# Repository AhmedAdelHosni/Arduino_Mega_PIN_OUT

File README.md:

# Arduino_Mega_PIN_OUT
Board layout pcb for expanding the Arduino Mega pin to Terminal block 5 mm pitch.

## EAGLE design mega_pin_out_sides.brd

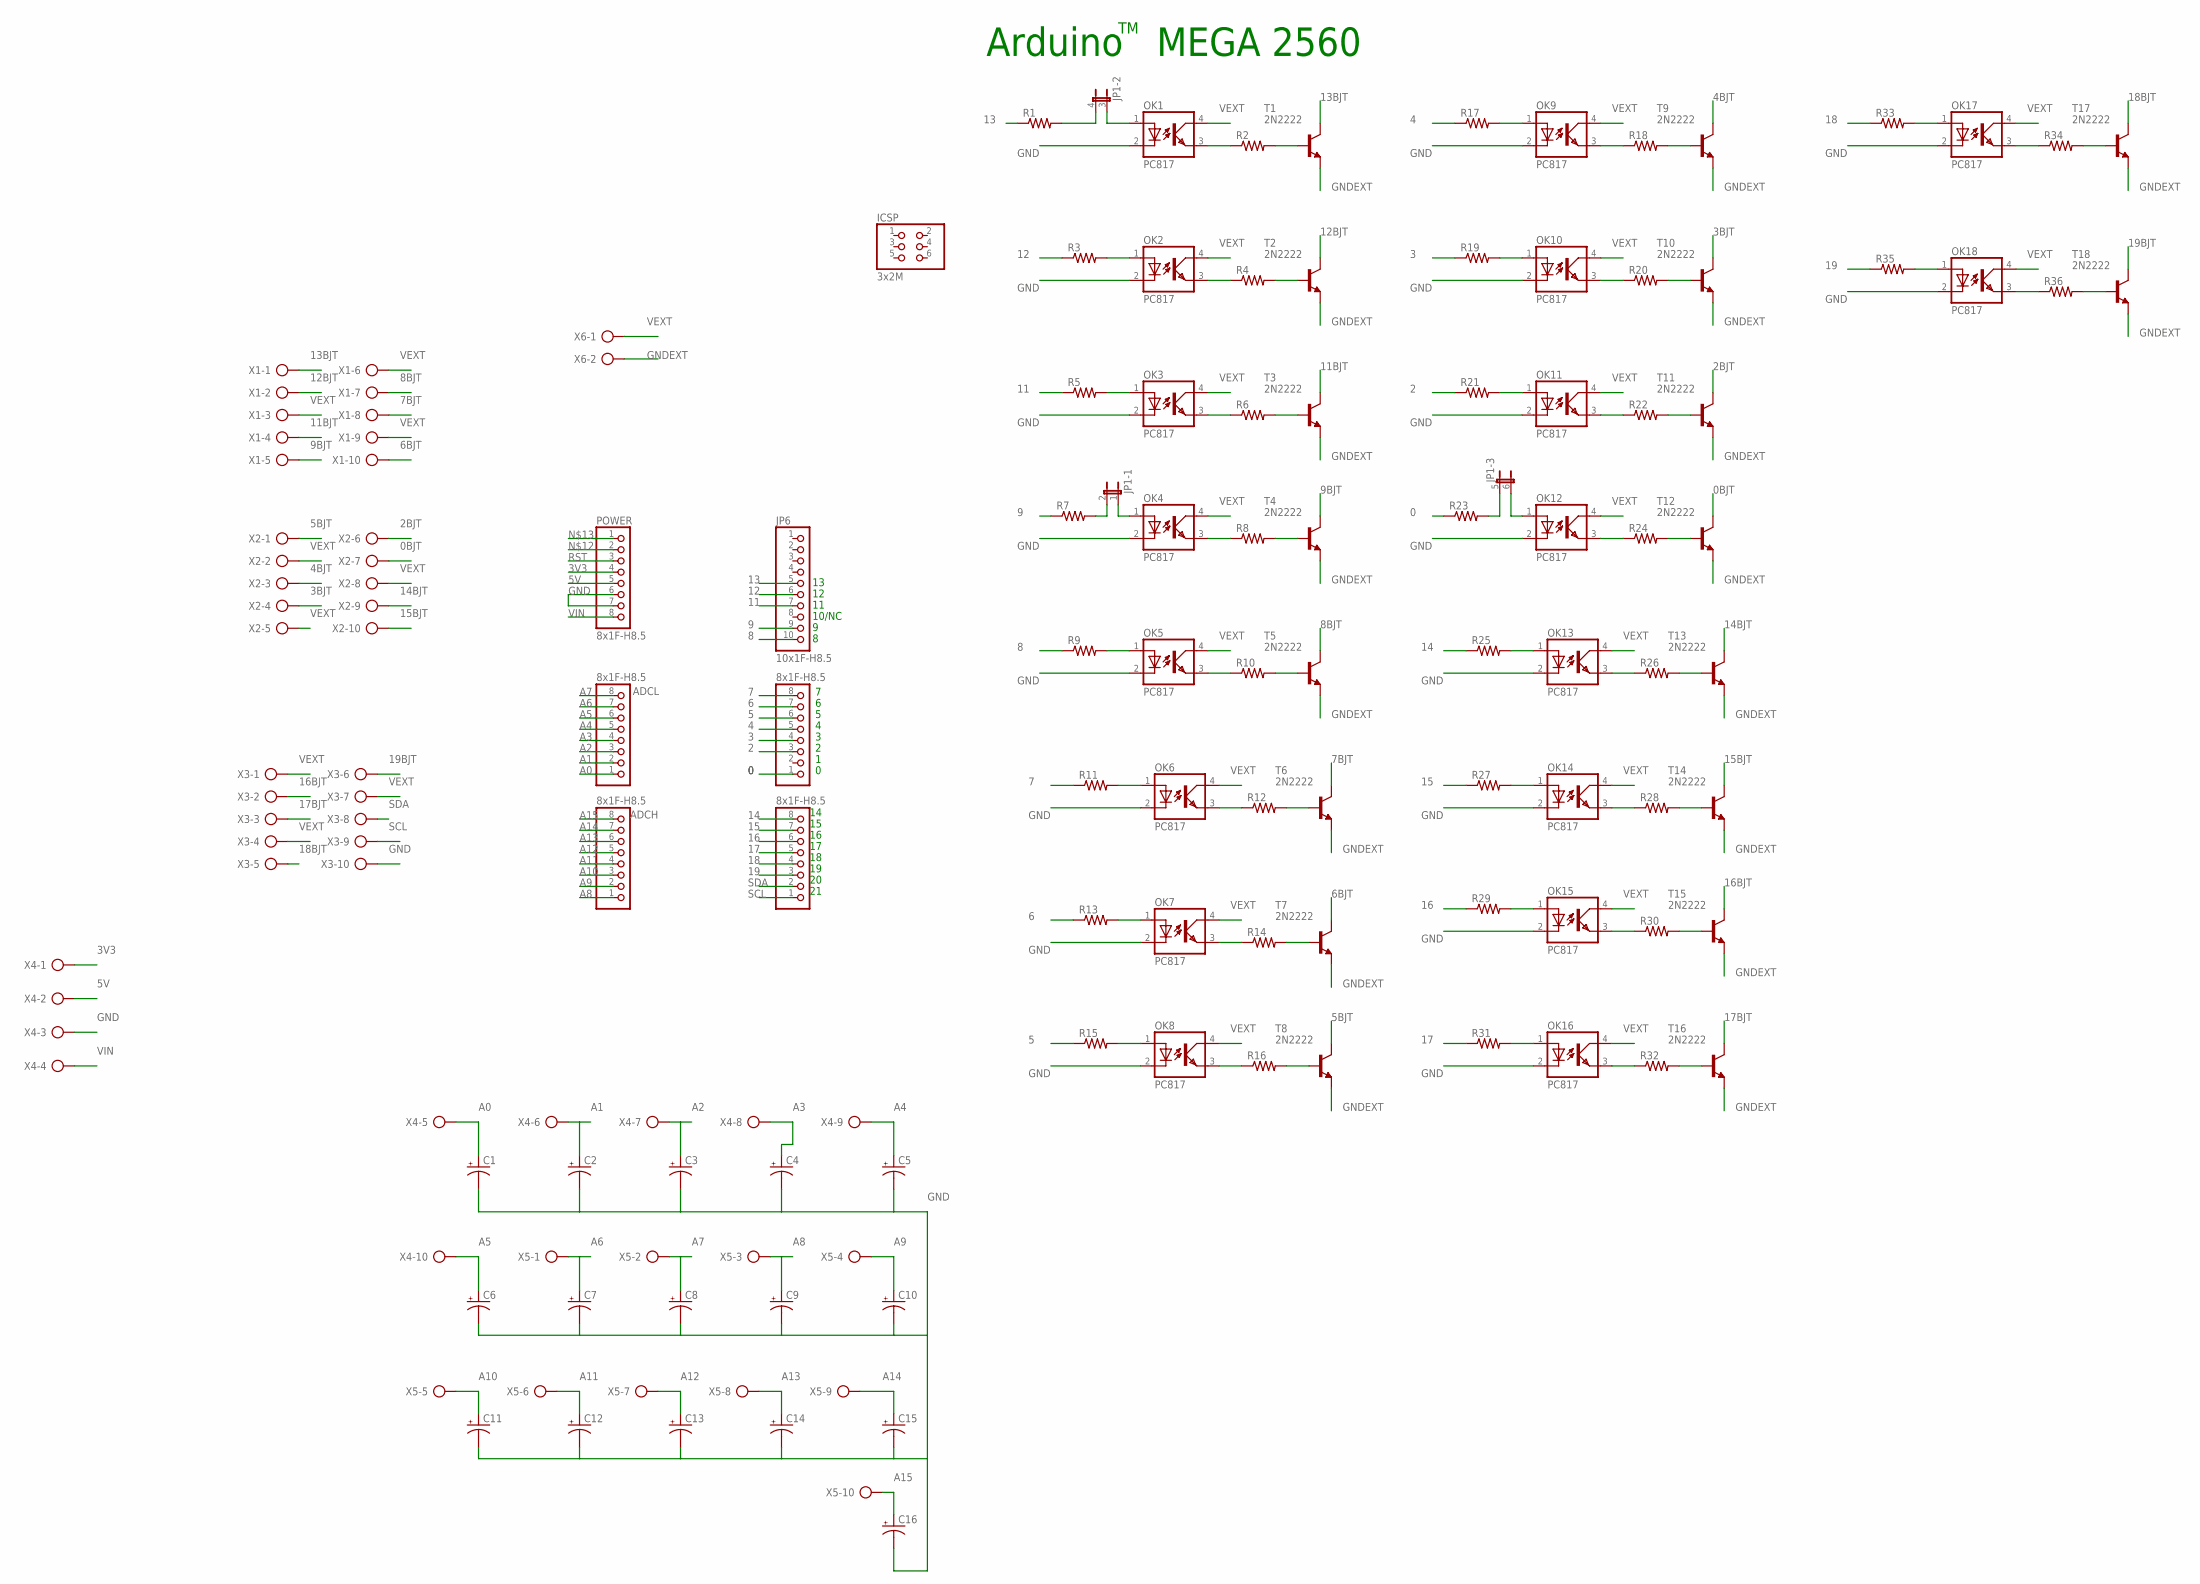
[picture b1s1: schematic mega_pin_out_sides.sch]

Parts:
ADCH: 8x1F-H8.5; 1X08
ADCL: 8x1F-H8.5; 1X08
C1, C2, C3, C4, C5, C6, C7, C8, C9, C10, C11, C12, C13, C14, C15, C16: CPOL-USE2-4; E2-4
COMMUNICATION: 8x1F-H8.5; 1X08
ICSP: 3x2M; 2X03
JP1: JP3QE; JP3Q
JP6: 10x1F-H8.5; 1X10
OK1, OK2, OK3, OK4, OK5, OK6, OK7, OK8, OK9, OK10, OK11, OK12, OK13, OK14, OK15, OK16, OK17, OK18: PC817; DIL04
POWER: 8x1F-H8.5; 1X08
PWML: 8x1F-H8.5; 1X08
R1, R2, R3, R4, R5, R6, R7, R8, R9, R10, R11, R12, R13, R14, R15, R16, R17, R18, R19, R20, R21, R22, R23, R24, R25, R26, R27, R28, R29, R30, R31, R32, R33, R34, R35, R36: R-US_M1206; M1206
T1, T2, T3, T4, T5, T6, T7, T8, T9, T10, T11, T12, T13, T14, T15, T16, T17, T18: 2N2222; TO18
X1, X2, X3, X4, X5: AK500/10
X6: AK500/2

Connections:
0: PWML.1, R23.1
0BJT: T12.3 (C), X2.7
2: PWML.3, R21.1
2BJT: T11.3 (C), X2.6
3: PWML.4, R19.1
3BJT: T10.3 (C), X2.4
3V3: POWER.4, X4.1
4: PWML.5, R17.1
4BJT: T9.3 (C), X2.3
5: PWML.6, R15.1
5BJT: T8.3 (C), X2.1
5V: POWER.5, X4.2
6: PWML.7, R13.1
6BJT: T7.3 (C), X1.10
7: PWML.8, R11.1
7BJT: T6.3 (C), X1.8
8: JP6.10, R9.1
8BJT: T5.3 (C), X1.7
9: JP6.9, R7.1
9BJT: T4.3 (C), X1.5
11: JP6.7, R5.1
11BJT: T3.3 (C), X1.4
12: JP6.6, R3.1
12BJT: T2.3 (C), X1.2
13: JP6.5, R1.1
13BJT: T1.3 (C), X1.1
14: COMMUNICATION.8, R25.1
14BJT: T13.3 (C), X2.9
15: COMMUNICATION.7, R27.1
15BJT: T14.3 (C), X2.10
16: COMMUNICATION.6, R29.1
16BJT: T15.3 (C), X3.2
17: COMMUNICATION.5, R31.1
17BJT: T16.3 (C), X3.3
18: COMMUNICATION.4, R33.1
18BJT: T17.3 (C), X3.5
19: COMMUNICATION.3, R35.1
19BJT: T18.3 (C), X3.6
A0: ADCL.1, C1.+, X4.5
A1: ADCL.2, C2.+, X4.6
A2: ADCL.3, C3.+, X4.7
A3: ADCL.4, C4.+, X4.8
A4: ADCL.5, C5.+, X4.9
A5: ADCL.6, C6.+, X4.10
A6: ADCL.7, C7.+, X5.1
A7: ADCL.8, C8.+, X5.2
A8: ADCH.1, C9.+, X5.3
A9: ADCH.2, C10.+, X5.4
A10: ADCH.3, C11.+, X5.5
A11: ADCH.4, C12.+, X5.6
A12: ADCH.5, C13.+, X5.7
A13: ADCH.6, C14.+, X5.8
A14: ADCH.7, C15.+, X5.9
A15: ADCH.8, C16.+, X5.10
GND: C1.-, C2.-, C3.-, C4.-, C5.-, C6.-, C7.-, C8.-, C9.-, C10.-, C11.-, C12.-, C13.-, C14.-, C15.-, C16.-, OK1.2 (C), OK2.2 (C), OK3.2 (C), OK4.2 (C), OK5.2 (C), OK6.2 (C), OK7.2 (C), OK8.2 (C), OK9.2 (C), OK10.2 (C), OK11.2 (C), OK12.2 (C), OK13.2 (C), OK14.2 (C), OK15.2 (C), OK16.2 (C), OK17.2 (C), OK18.2 (C), POWER.6, POWER.7, X3.10, X4.3
GNDEXT: T1.1 (E), T2.1 (E), T3.1 (E), T4.1 (E), T5.1 (E), T6.1 (E), T7.1 (E), T8.1 (E), T9.1 (E), T10.1 (E), T11.1 (E), T12.1 (E), T13.1 (E), T14.1 (E), T15.1 (E), T16.1 (E), T17.1 (E), T18.1 (E), X6.2
unnamed: JP1.4 (2), R1.2
unnamed: OK1.3 (EMIT), R2.1
unnamed: R2.2, T1.2 (B)
unnamed: OK2.1 (A), R3.2
unnamed: OK2.3 (EMIT), R4.1
unnamed: R4.2, T2.2 (B)
unnamed: OK3.1 (A), R5.2
unnamed: JP1.3 (1), OK1.1 (A)
unnamed: JP1.6 (2), OK12.1 (A)
unnamed: JP1.1, OK4.1 (A)
unnamed: OK5.1 (A), R9.2
unnamed: OK5.3 (EMIT), R10.1
unnamed: OK3.3 (EMIT), R6.1
unnamed: R6.2, T3.2 (B)
unnamed: JP1.2, R7.2
unnamed: OK4.3 (EMIT), R8.1
unnamed: R8.2, T4.2 (B)
unnamed: R10.2, T5.2 (B)
unnamed: OK6.1 (A), R11.2
unnamed: OK6.3 (EMIT), R12.1
unnamed: R12.2, T6.2 (B)
unnamed: OK7.1 (A), R13.2
unnamed: OK7.3 (EMIT), R14.1
unnamed: R14.2, T7.2 (B)
unnamed: OK8.1 (A), R15.2
unnamed: OK8.3 (EMIT), R16.1
unnamed: R16.2, T8.2 (B)
unnamed: OK9.1 (A), R17.2
unnamed: OK9.3 (EMIT), R18.1
unnamed: R18.2, T9.2 (B)
unnamed: OK10.1 (A), R19.2
unnamed: OK10.3 (EMIT), R20.1
unnamed: R20.2, T10.2 (B)
unnamed: OK11.1 (A), R21.2
unnamed: OK11.3 (EMIT), R22.1
unnamed: R22.2, T11.2 (B)
unnamed: OK16.1 (A), R31.2
unnamed: OK16.3 (EMIT), R32.1
unnamed: R32.2, T16.2 (B)
unnamed: JP1.5 (1), R23.2
unnamed: OK12.3 (EMIT), R24.1
unnamed: R24.2, T12.2 (B)
unnamed: OK13.1 (A), R25.2
unnamed: OK13.3 (EMIT), R26.1
unnamed: R26.2, T13.2 (B)
unnamed: OK14.1 (A), R27.2
unnamed: OK14.3 (EMIT), R28.1
unnamed: R28.2, T14.2 (B)
unnamed: OK15.1 (A), R29.2
unnamed: OK15.3 (EMIT), R30.1
unnamed: R30.2, T15.2 (B)
unnamed: OK18.1 (A), R35.2
unnamed: OK18.3 (EMIT), R36.1
unnamed: R36.2, T18.2 (B)
unnamed: OK17.1 (A), R33.2
unnamed: OK17.3 (EMIT), R34.1
unnamed: R34.2, T17.2 (B)
RST: POWER.3
SCL: COMMUNICATION.1, X3.9
SDA: COMMUNICATION.2, X3.8
VEXT: OK1.4 (COL), OK2.4 (COL), OK3.4 (COL), OK4.4 (COL), OK5.4 (COL), OK6.4 (COL), OK7.4 (COL), OK8.4 (COL), OK9.4 (COL), OK10.4 (COL), OK11.4 (COL), OK12.4 (COL), OK13.4 (COL), OK14.4 (COL), OK15.4 (COL), OK16.4 (COL), OK17.4 (COL), OK18.4 (COL), X1.3, X1.6, X1.9, X2.2, X2.5, X2.8, X3.1, X3.4, X3.7, X6.1
VIN: POWER.8, X4.4

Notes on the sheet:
10/NC
Arduino MEGA 2560

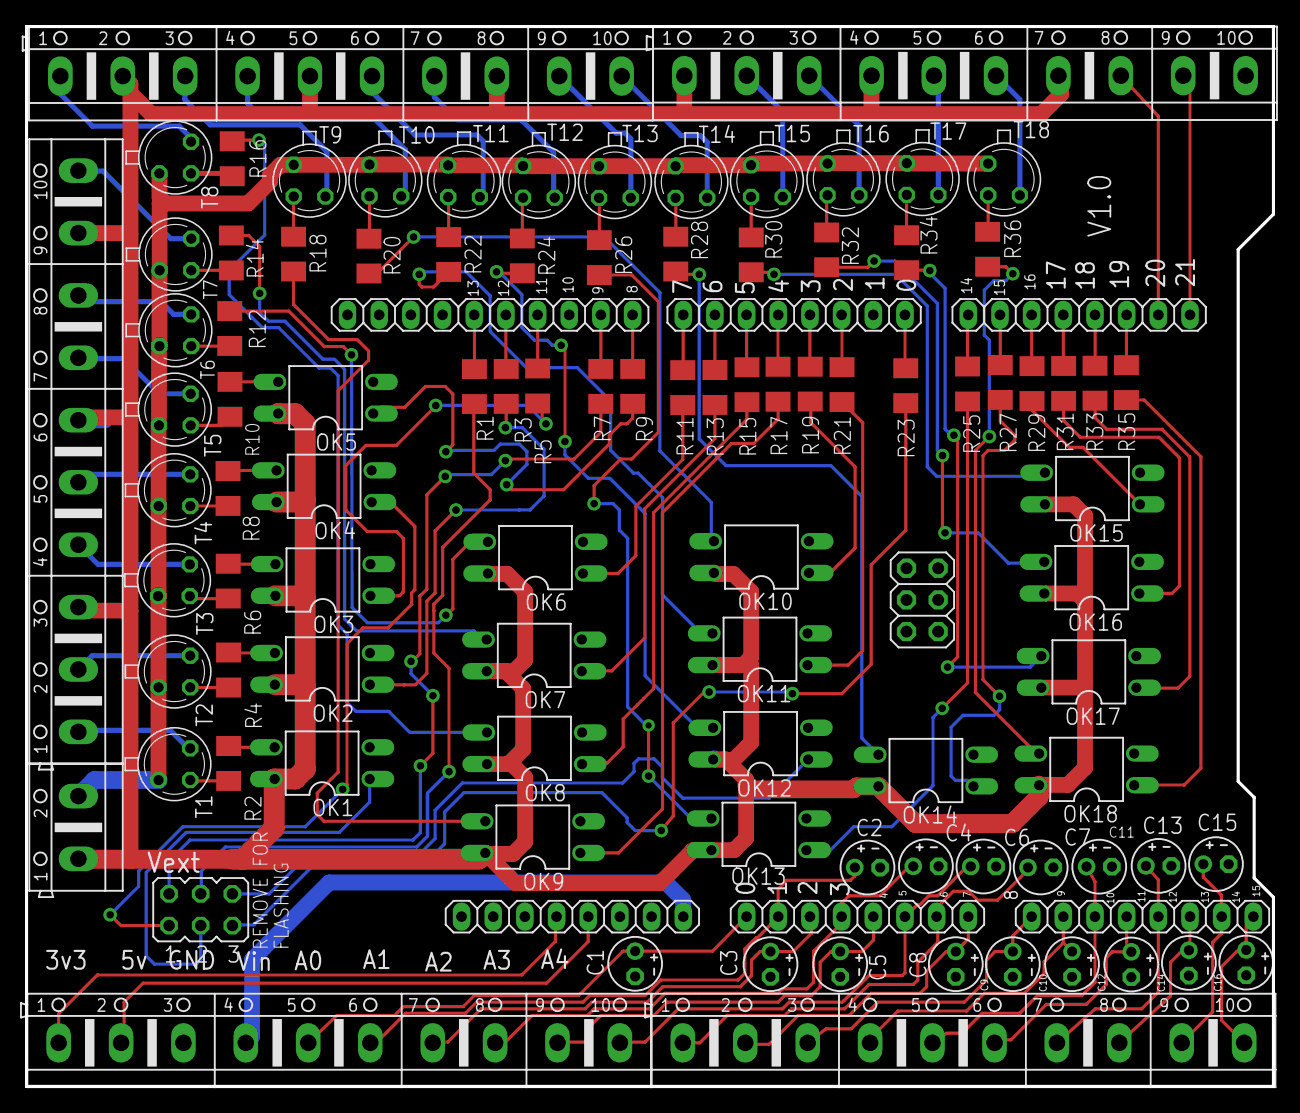
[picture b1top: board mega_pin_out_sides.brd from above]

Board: 2 copper layers, 100.0 x 85.0 mm, 102 parts (0 on the bottom side), 117 nets.

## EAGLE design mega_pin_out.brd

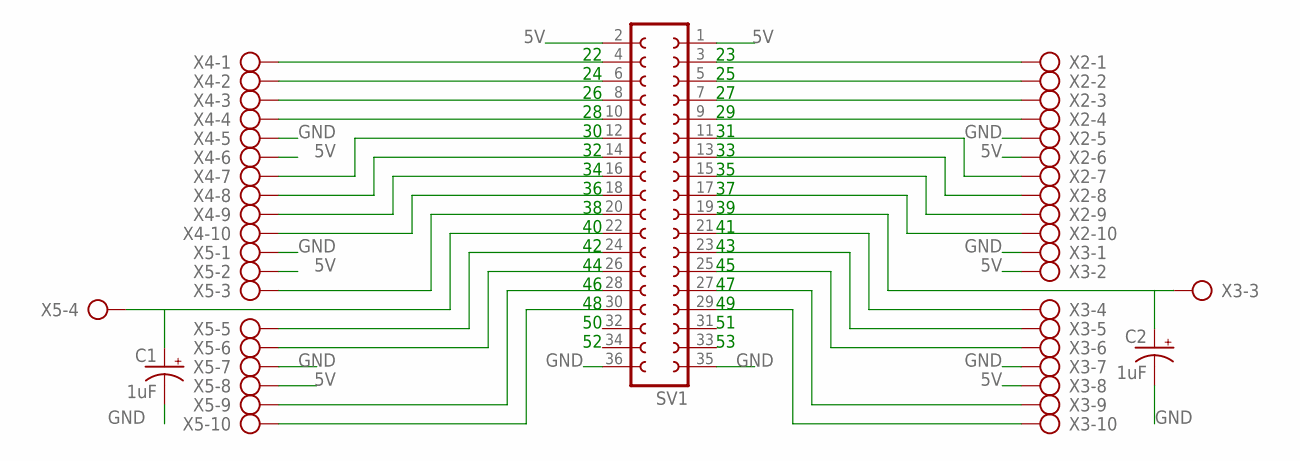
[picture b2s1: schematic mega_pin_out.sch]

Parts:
C1, C2: 1uF; E2-4
SV1: FE18-2
X2, X3, X4, X5: AK500/10

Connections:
5V: SV1.1, SV1.2, X2.6, X3.2, X3.8, X4.6, X5.2, X5.8
GND: C1.-, C2.-, SV1.35, SV1.36, X2.5, X3.1, X3.7, X4.5, X5.1, X5.7
I31: SV1.11, X2.7
I33: SV1.13, X2.8
I35: SV1.15, X2.9
I47: SV1.27, X3.9
I49: SV1.29, X3.10
unnamed: C2.+, SV1.19, X3.3
unnamed: SV1.20, X5.3
unnamed: SV1.3, X2.1
unnamed: SV1.5, X2.2
unnamed: SV1.7, X2.3
unnamed: SV1.9, X2.4
unnamed: SV1.17, X2.10
unnamed: SV1.21, X3.4
unnamed: SV1.23, X3.5
unnamed: SV1.25, X3.6
unnamed: SV1.4, X4.1
unnamed: SV1.6, X4.2
unnamed: SV1.8, X4.3
unnamed: SV1.10, X4.4
unnamed: SV1.12, X4.7
unnamed: SV1.14, X4.8
unnamed: SV1.16, X4.9
unnamed: SV1.18, X4.10
unnamed: C1.+, SV1.22, X5.4
unnamed: SV1.24, X5.5
unnamed: SV1.26, X5.6
unnamed: SV1.28, X5.9
unnamed: SV1.30, X5.10

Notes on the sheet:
23 25 27 29 31 33 35 37 39 41 43 45 47 49 51 53
22 24 26 28 30 32 34 36 38 40 42 44 46 48 50 52

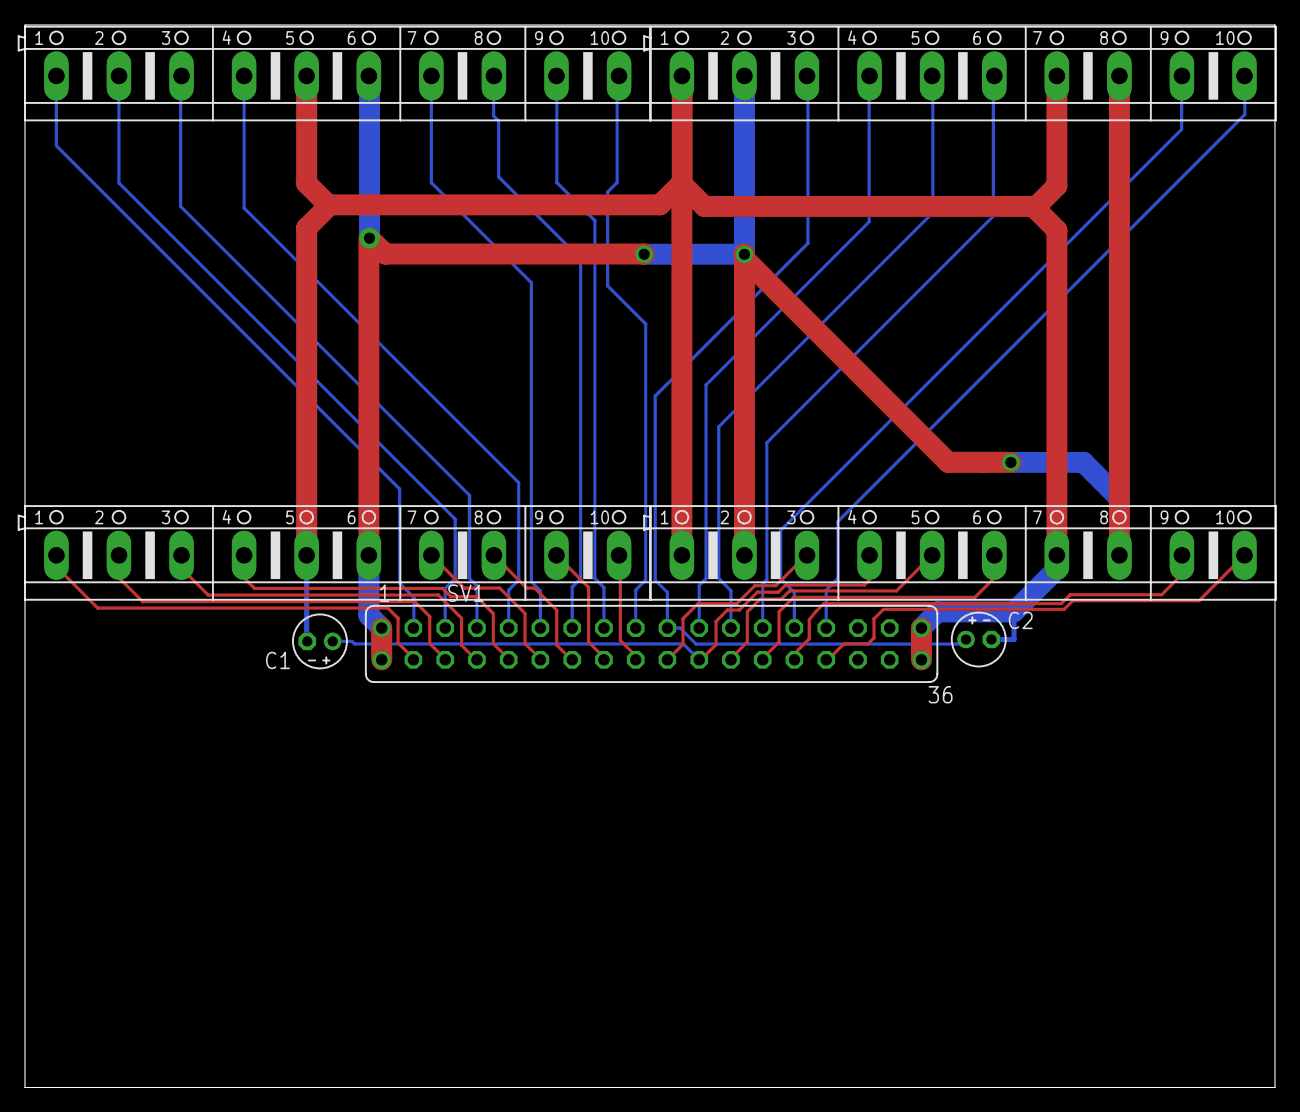
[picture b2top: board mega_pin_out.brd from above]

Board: 2 copper layers, 100.0 x 85.0 mm, 7 parts (0 on the bottom side), 30 nets.

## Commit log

2018-12-10 Add sch and brd files for first commit of project
    Begun designing of the double pin group.
2018-12-16 Full reroute of 2x18 female pins
    - Fixed the female pins pcb layout part size
    - Reroute all pins
2018-12-17 First trial to implement side terminals
    In this commit each block was grouped together. The block has 2 resistors and a pc817.
    TODO: Try to group by component.
2018-12-17 [SIDES] Group same components together
    - Grouped same components together and till now this looks a better design solution. to be continued.
2018-12-19 Continue side Schematic design and layout
    Almost finished first trail for board layout.
2018-12-20 [SIDES] New design proposal
    - In this commit the layout was completely changed. Opto are grouped in the center while BJT was beside the terminal blocks.
    TODO: complete the Analogue side.
2018-12-22 [BACK] Added capacitors for PIN 39 & 40 and others
    * Schematic:
    - Added text field for pin numbers name
    - Added charging capacitors for pin 39 & 40 which are used as AC light state detectors.
    * Board
    - Increased board layout from 100x80 to 100x85
    - Increased clearance between terminal blocks to ~22.86 mm which was tested on breadboard to be easier during wiring.
2018-12-24 [SIDES] Fix major issue where GND was common
    - Fix a major bug in the design where the Vext GND and Arduino GND were common. They have been isolated correctly.
2018-12-25 [SIDES] Fix DRC Errors
    - Fixed all DRC Errors which were related to silk screens mainly.
    - Re routed some pins for a better path.
2019-01-24 [BUG][MAJOR] Fix wrong orientation of pin header
    - Pin header connections were all wrong and mirrored. To fix it, I mirrored the header in schematics and rerouted the wrong pins.
    - Added labels
    - increased the distance between the two terminal block rows to ~31 cm
2019-01-24 [SIDES] Added header jumper pins for Flashing
    - During Flashing or Reset Pin 13, 9 & 0 flashes several times and this will trigger the relays. A header jumper to be removed during flashing and after start up they are back again in place.
2019-01-29 [SIDES] Placed Vext & Gext on a separate layer
    External voltage is routed on the top layer instead to be isolated from the ground plane.
2019-01-31 [SIDES] Review of board and enhancements
    - changed capacitors orientation.
    - Changed some pcb traces
2019-02-03 [SIDED] Review and enhancement cont.
    - Changed some traces
